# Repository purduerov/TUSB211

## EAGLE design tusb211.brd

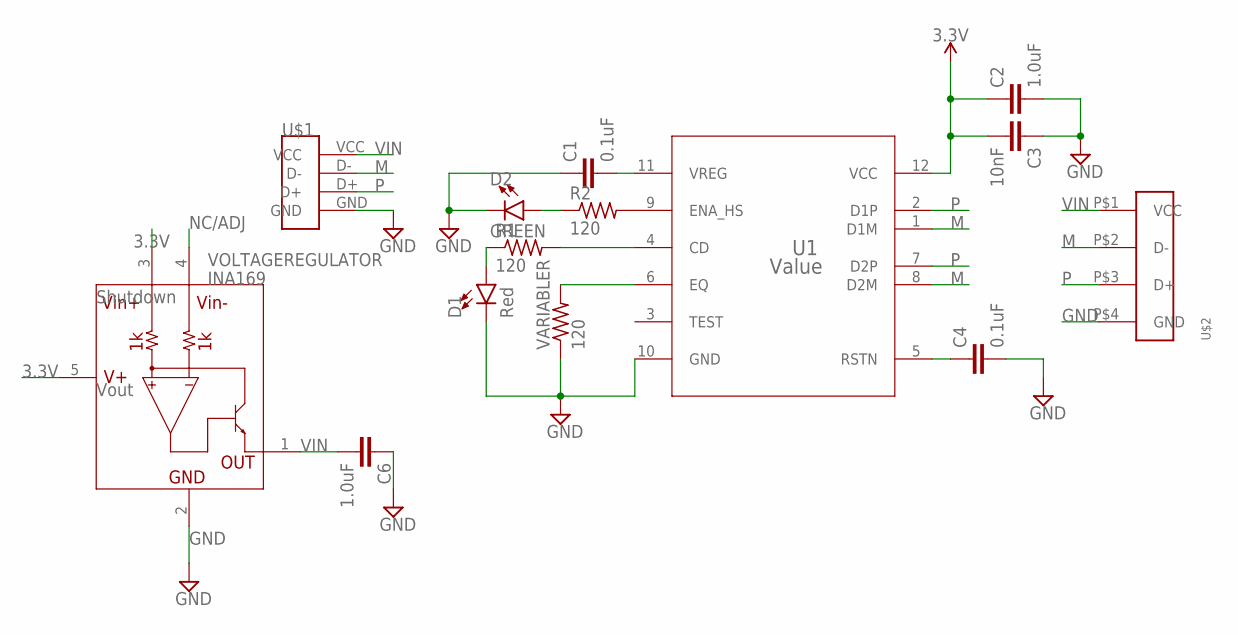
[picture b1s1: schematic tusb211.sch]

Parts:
C1, C4: 0.1uF; 0603
C2, C6: 1.0uF; 0603
C3: 10nF; 0603
D1: Red; LED-0603
D2: GREEN; LED-0603
R1, R2: 120; R0805
U1: Value; RWB0012A
U$1: TYPEAUSB
U$2: USB; USBSMD
VARIABLER: 120; R0805
VOLTAGEREGULATOR: INA169; SOT23-5

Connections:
3.3V: C2.1, C3.2, U1.12 (VCC), VOLTAGEREGULATOR.3 (VIN+), VOLTAGEREGULATOR.5 (V+)
GND: C1.1, C2.2, C3.1, C4.2, C6.1, D1.C, D2.C, U1.10 (GND), U$1.GND, U$2.P$4 (GND), VARIABLER.1, VOLTAGEREGULATOR.2 (GND)
M: U1.1 (D1M), U1.8 (D2M), U$1.D-, U$2.P$2 (D-)
unnamed: C1.2, U1.11 (VREG)
unnamed: D1.A, R1.1
unnamed: R1.2, U1.4 (CD)
unnamed: C4.1, U1.5 (RSTN)
unnamed: U1.6 (EQ), VARIABLER.2
unnamed: R2.2, U1.9 (ENA_HS)
unnamed: D2.A, R2.1
NC/ADJ: VOLTAGEREGULATOR.4 (VIN-)
P: U1.2 (D1P), U1.7 (D2P), U$1.D+, U$2.P$3 (D+)
VIN: C6.2, U$1.VCC, U$2.P$1 (VCC), VOLTAGEREGULATOR.1 (OUT)

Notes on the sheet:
Shutdown
Vout

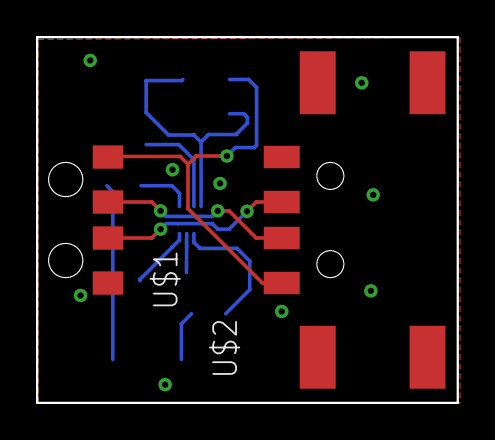
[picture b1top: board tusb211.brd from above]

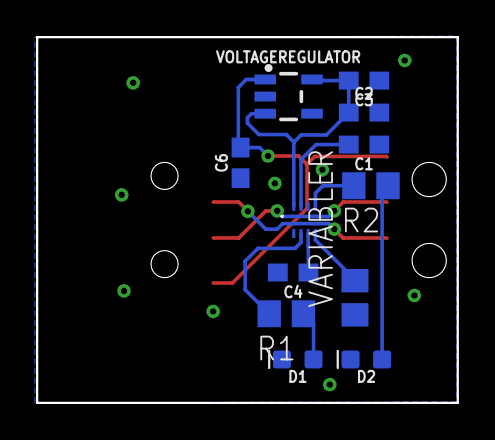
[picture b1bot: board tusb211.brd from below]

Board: 2 copper layers, 23.4 x 20.3 mm, 14 parts (12 on the bottom side), 12 nets.

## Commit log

2017-09-28 TUSB board
2017-09-28 Added schematic
2017-09-30 created empty schematic
2017-09-30 Test
2017-09-30 Revert "Initial commit"
    This reverts commit 68040bd0c05e8baf28e98f1afe2d8cb1636d6903.
2017-09-30 added TUSB211 part
2017-09-30 Added female usb
2017-09-30 removed lock
2017-10-14 version 1
2017-10-14 added project file
2017-10-15 Added gitignore
2017-10-19 changed name, fixed DRC errors
2017-10-20 Got rid of PCB USB, added led, added spot for EQ resistor, fixed wiring
2017-10-20 Added BOM
2017-10-21 changed trace widths
2017-10-21 D+ and D- have same length
2017-10-28 updated BOM
2017-11-11 Added Elecrow cam job

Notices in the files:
parts and their libraries:
SparkFun-Capacitors: Licensing: Creative Commons ShareAlike 4.0 International - https://creativecommons.org/licenses/by-sa/4.0
